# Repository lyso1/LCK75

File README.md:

# LCK75

This is an altered version of the [original LCK75](https://github.com/lyso1/LCK75) created by [Lysol](https://github.com/lyso1).

Changes made to the original project:
  - changed folder/file hierarchy to make it more comprehensive;
  - removed wave art from the top of the main board;
  - removed gigantic logo from the bottom plate;

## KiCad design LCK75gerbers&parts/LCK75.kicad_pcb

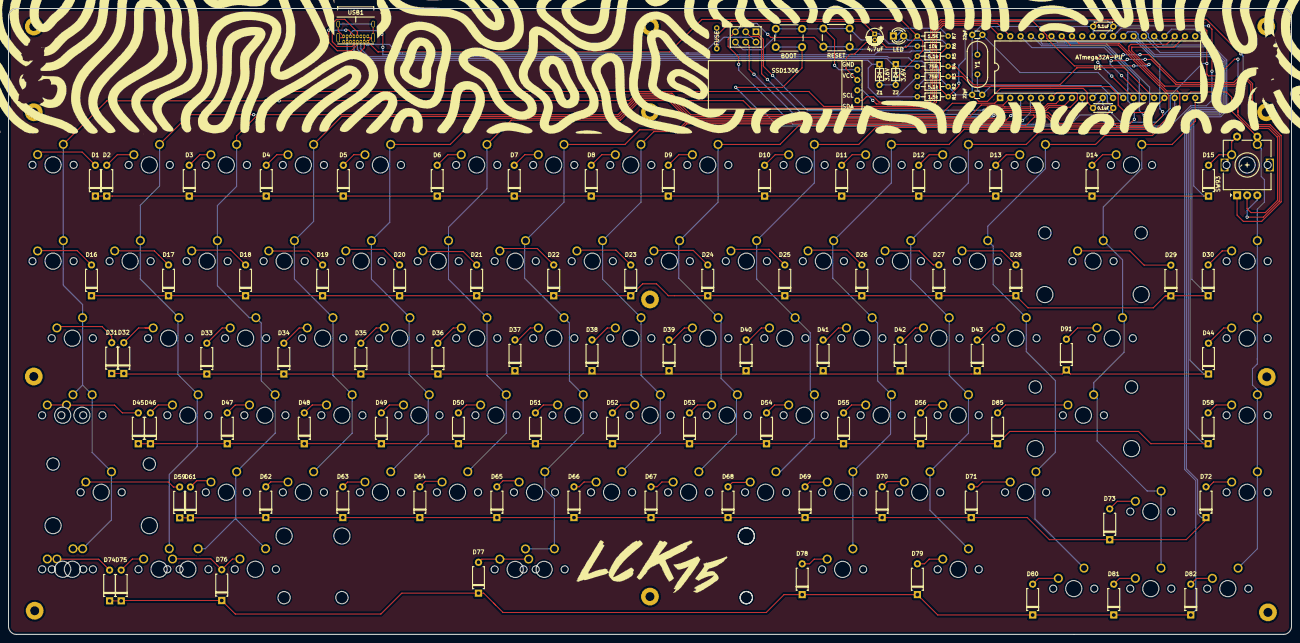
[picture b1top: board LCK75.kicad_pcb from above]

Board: 2 copper layers, 317.3 x 154.8 mm, 192 parts (1 on the bottom side), 124 nets.

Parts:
C1, C2: 22pF; C_Disc_D3.0mm_W1.6mm_P2.50mm
C3: 4.7uF; CP_Radial_D4.0mm_P1.50mm
C4, C5: 0.1uF; C_Disc_D4.3mm_W1.9mm_P5.00mm
D1, D2, D3, D4, D5, D6, D7, D8, D9, D10, D11, D12, D13, D14, D15, D16, D17, D18, D19, D20, D21, D22, D23, D24, D25, D26, D27, D28, D29, D30, D31, D32, D33, D34, D35, D36, D37, D38, D39, D40, D41, D42, D43, D44, D45, D46, D47, D48, D49, D50, D51, D52, D53, D54, D55, D56, D58, D59, D61, D62, D63, D64, D65, D66, D67, D68, D69, D70, D71, D72, D73, D74, D75, D76, D77, D78, D79, D80, D81, D82, D85, D91: 1N4148; D_A-405_P7.62mm_Horizontal
F1: 500mA; polyfuse_5.1mm
J1: AVR-ISP-6; AVR_ICSP_3x2
LED: POWER; LED_D3.0mm
R1: 1.5k; R_Axial_DIN0204_L3.6mm_D1.6mm_P7.62mm_Horizontal
R2, R5: 5.1k; R_Axial_DIN0204_L3.6mm_D1.6mm_P7.62mm_Horizontal
R3, R4: 75R; R_Axial_DIN0204_L3.6mm_D1.6mm_P7.62mm_Horizontal
R6: 10k; R_Axial_DIN0204_L3.6mm_D1.6mm_P7.62mm_Horizontal
R7: 1.5K; R_Axial_DIN0204_L3.6mm_D1.6mm_P7.62mm_Horizontal
SSD1306: OLED; ssd1306 128x32 oled
SW1, SW2, SW3, SW4, SW5, SW6, SW7, SW8, SW9, SW10, SW11, SW12, SW13, SW14, SW15, SW16, SW17, SW18, SW19, SW20, SW21, SW22, SW23, SW24, SW25, SW26, SW27, SW28, SW30, SW32, SW33, SW34, SW35, SW36, SW37, SW38, SW39, SW40, SW41, SW42, SW43, SW45, SW46, SW48, SW49, SW50, SW51, SW52, SW53, SW54, SW55, SW56, SW57, SW58, SW61, SW65, SW66, SW67, SW68, SW69, SW70, SW71, SW72, SW73, SW74, SW76, SW77, SW84, SW85, SW86: SW_SPST; MXOnly-1U-NoLED
SW29: SW_SPST; MXOnly-2U-NoLED
SW31, SW44, SW82, SW83, SW88, SW89: SW_SPST; MXOnly-1.5U-NoLED
SW47, SW75: SW_SPST; MXOnly-1.75U-NoLED
SW60, SW63: SW_SPST; MXOnly-2.25U-NoLED
SW78, SW79, SW80: SW_SPST; MXOnly-1.25U-NoLED
SW81: SW_SPST; MXOnly-7U-ReversedStabilizers-NoLED
SW87, SW91: SW_PUSH-keyboard_parts; SW_PUSH_6mm
SW90: SW_SPST; MXOnly-6.25U-ReversedStabilizers-NoLED
SW93: Rotary_Encoder_Switch; RotaryEncoder_Alps_EC11E-Switch_Vertical_H20mm-new
U1: ATmega32A-PU; DIP-40_W15.24mm
USB1: Type-C_USB_C_GCT_USB4085; USB_C_GCT_USB4085
Y1: Crystal; Crystal_HC49-4H_Vertical
Z1, Z2: 3.6V; D_DO-35_SOD27_P5.08mm_Horizontal

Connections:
D+: R4.1, U1.16
D-: R3.1, U1.17
EC11-A: SW93.A, U1.14
EC11-B: SW93.B, U1.15
EC11-GND: C1.2, C2.2, C3.2, C4.2, C5.2, J1.6, R2.1, R5.2, R7.2, SSD1306.4, SW87.1, SW91.1, SW93.C, U1.11, U1.31, USB1.A1, USB1.B1, USB1.B12, USB1.S1, Z1.2, Z2.2
MISO: J1.1, U1.7
MOSI: J1.4, U1.6
unnamed: C1.1, U1.13, Y1.1
unnamed: C2.1, U1.12, Y1.2
unnamed: D1.2, SW1.1
unnamed: D2.2, SW2.1
unnamed: D3.2, SW3.1
unnamed: D4.2, SW4.1
unnamed: D5.2, SW5.1
unnamed: D6.2, SW6.1
unnamed: D7.2, SW7.1
unnamed: D8.2, SW8.1
unnamed: D9.2, SW9.1
unnamed: D10.2, SW10.1
unnamed: D11.2, SW11.1
unnamed: D12.2, SW12.1
unnamed: D13.2, SW13.1
unnamed: D14.2, SW14.1
unnamed: D15.2, SW15.1, SW93.S2
unnamed: D16.2, SW16.1
unnamed: D17.2, SW17.1
unnamed: D18.2, SW18.1
unnamed: D19.2, SW19.1
unnamed: D20.2, SW20.1
unnamed: D21.2, SW21.1
unnamed: D22.2, SW22.1
unnamed: D23.2, SW23.1
unnamed: D24.2, SW24.1
unnamed: D25.2, SW25.1
unnamed: D26.2, SW26.1
unnamed: D27.2, SW27.1
unnamed: D28.2, SW28.1
unnamed: D29.2, SW29.1
unnamed: D30.2, SW30.1
unnamed: D31.2, SW31.1
unnamed: D32.2, SW32.1
unnamed: D33.2, SW33.1
unnamed: D34.2, SW34.1
unnamed: D35.2, SW35.1
unnamed: D36.2, SW36.1
unnamed: D37.2, SW37.1
unnamed: D38.2, SW38.1
unnamed: D39.2, SW39.1
unnamed: D40.2, SW40.1
unnamed: D41.2, SW41.1
unnamed: D42.2, SW42.1
unnamed: D43.2, SW43.1
unnamed: D44.2, SW45.1
unnamed: D45.2, SW46.1, SW47.1
unnamed: D46.2, SW48.1
unnamed: D47.2, SW49.1
unnamed: D48.2, SW50.1
unnamed: D49.2, SW51.1
unnamed: D50.2, SW52.1
unnamed: D51.2, SW53.1
unnamed: D52.2, SW54.1
unnamed: D53.2, SW55.1
unnamed: D54.2, SW56.1
unnamed: D55.2, SW57.1
unnamed: D56.2, SW58.1
unnamed: D58.2, SW61.1
unnamed: D59.2, SW63.1
unnamed: D61.2, SW65.1
unnamed: D62.2, SW66.1
unnamed: D63.2, SW67.1
unnamed: D64.2, SW68.1
unnamed: D65.2, SW69.1
unnamed: D66.2, SW70.1
unnamed: D67.2, SW71.1
unnamed: D68.2, SW72.1
unnamed: D69.2, SW73.1
unnamed: D70.2, SW74.1
unnamed: D71.2, SW75.1
unnamed: D72.2, SW76.1
unnamed: D73.2, SW77.1
unnamed: D74.2, SW78.1, SW88.1
unnamed: D75.2, SW79.1
unnamed: D76.2, SW80.1, SW89.1
unnamed: D77.2, SW81.1, SW90.1
unnamed: D78.2, SW82.1
unnamed: D79.2, SW83.1
unnamed: D80.2, SW84.1
unnamed: D81.2, SW85.1
unnamed: D82.2, SW86.1
unnamed: R1.2, R3.2, USB1.A7, USB1.B7, Z1.1
unnamed: R4.2, USB1.A6, USB1.B6, Z2.1
unnamed: D85.2, SW60.1
unnamed: D91.2, SW44.1
unnamed: LED.1, R7.1
unnamed: R2.2, USB1.A5
unnamed: R5.1, USB1.B5
SCK: J1.3, U1.8
VCC: F1.2, USB1.A4, USB1.A9, USB1.B4, USB1.B9
boot: SW87.2, U1.18
col0: SW1.2, SW16.2, SW31.2, SW46.2, SW47.2, SW63.2, SW78.2, SW88.2, U1.40
col1: SW2.2, SW17.2, SW32.2, SW48.2, SW79.2, U1.1
col2: SW3.2, SW18.2, SW33.2, SW49.2, SW65.2, SW80.2, SW89.2, U1.39
col3: SW4.2, SW19.2, SW34.2, SW50.2, SW66.2, U1.2
col4: SW5.2, SW20.2, SW35.2, SW51.2, SW67.2, U1.38
col5: SW6.2, SW21.2, SW36.2, SW52.2, SW68.2, U1.3
col6: SW7.2, SW22.2, SW37.2, SW53.2, SW69.2, SW81.2, SW90.2, U1.37
col7: SW8.2, SW23.2, SW38.2, SW54.2, SW70.2, U1.4
col8: SW9.2, SW24.2, SW39.2, SW55.2, SW71.2, U1.36
col9: SW10.2, SW25.2, SW40.2, SW56.2, SW72.2, U1.5
col10: SW11.2, SW26.2, SW41.2, SW57.2, SW73.2, SW82.2, U1.35
col11: SW12.2, SW27.2, SW42.2, SW58.2, SW74.2, SW83.2, U1.34
col12: SW13.2, SW28.2, SW43.2, SW75.2, SW84.2, U1.33
col13: SW14.2, SW29.2, SW44.2, SW60.2, SW77.2, SW85.2, U1.20
col14: SW15.2, SW30.2, SW45.2, SW61.2, SW76.2, SW86.2, SW93.S1, U1.19
oledSCL: SSD1306.2, U1.22
oledSDA: SSD1306.1, U1.23
oledVCC: C3.1, C4.1, C5.1, F1.1, J1.2, LED.2, R1.1, R6.1, SSD1306.3, U1.10, U1.30
reset: J1.5, R6.2, SW91.2, U1.9
row0: D1.1, D2.1, D3.1, D4.1, D5.1, D6.1, D7.1, D8.1, D9.1, D10.1, D11.1, D12.1, D13.1, D14.1, D15.1, U1.24
row1: D16.1, D17.1, D18.1, D19.1, D20.1, D21.1, D22.1, D23.1, D24.1, D25.1, D26.1, D27.1, D28.1, D29.1, D30.1, U1.25
row2: D31.1, D32.1, D33.1, D34.1, D35.1, D36.1, D37.1, D38.1, D39.1, D40.1, D41.1, D42.1, D43.1, D44.1, D91.1, U1.29
row3: D45.1, D46.1, D47.1, D48.1, D49.1, D50.1, D51.1, D52.1, D53.1, D54.1, D55.1, D56.1, D58.1, D85.1, U1.26
row4: D59.1, D61.1, D62.1, D63.1, D64.1, D65.1, D66.1, D67.1, D68.1, D69.1, D70.1, D71.1, D72.1, D73.1, U1.28
row5: D74.1, D75.1, D76.1, D77.1, D78.1, D79.1, D80.1, D81.1, D82.1, U1.27

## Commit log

2020-10-01 added some of the pcb design parts
2020-10-02 Add files via upload
    keymap files that were due to be uploaded
2020-10-02 changed some lines in the keymap files
2020-10-02 old keymaps
    old
2020-10-02 rearranging
2020-10-03 changed keymap files
2020-10-04 made changes to keymap files
2020-10-04 got rid of the old keymap
2020-10-04 rename
2020-10-04 editted some keymap files
2021-01-09 final qmk files for the lck75
    final qmk files for lck75
2021-01-10 qmk stuff
    qmk stuff
2021-04-14 updated for rev 1 productions files
2021-04-14 renamed files
2021-04-14 most up to date qmk files
2021-04-14 added cc
2021-04-14 formatting
2021-04-14 add images
2021-04-14 changed file name
2021-06-10 missing files i forgot
2023-03-02 initial cleanup:
    - changed folder/file structure to make easier to identify the
    different components;
    - removed wave art and giant logo from the main and bottom pcbs
    respectively;
    - updated gerber files for the main and bottom pcbs;
    - updated board images;
